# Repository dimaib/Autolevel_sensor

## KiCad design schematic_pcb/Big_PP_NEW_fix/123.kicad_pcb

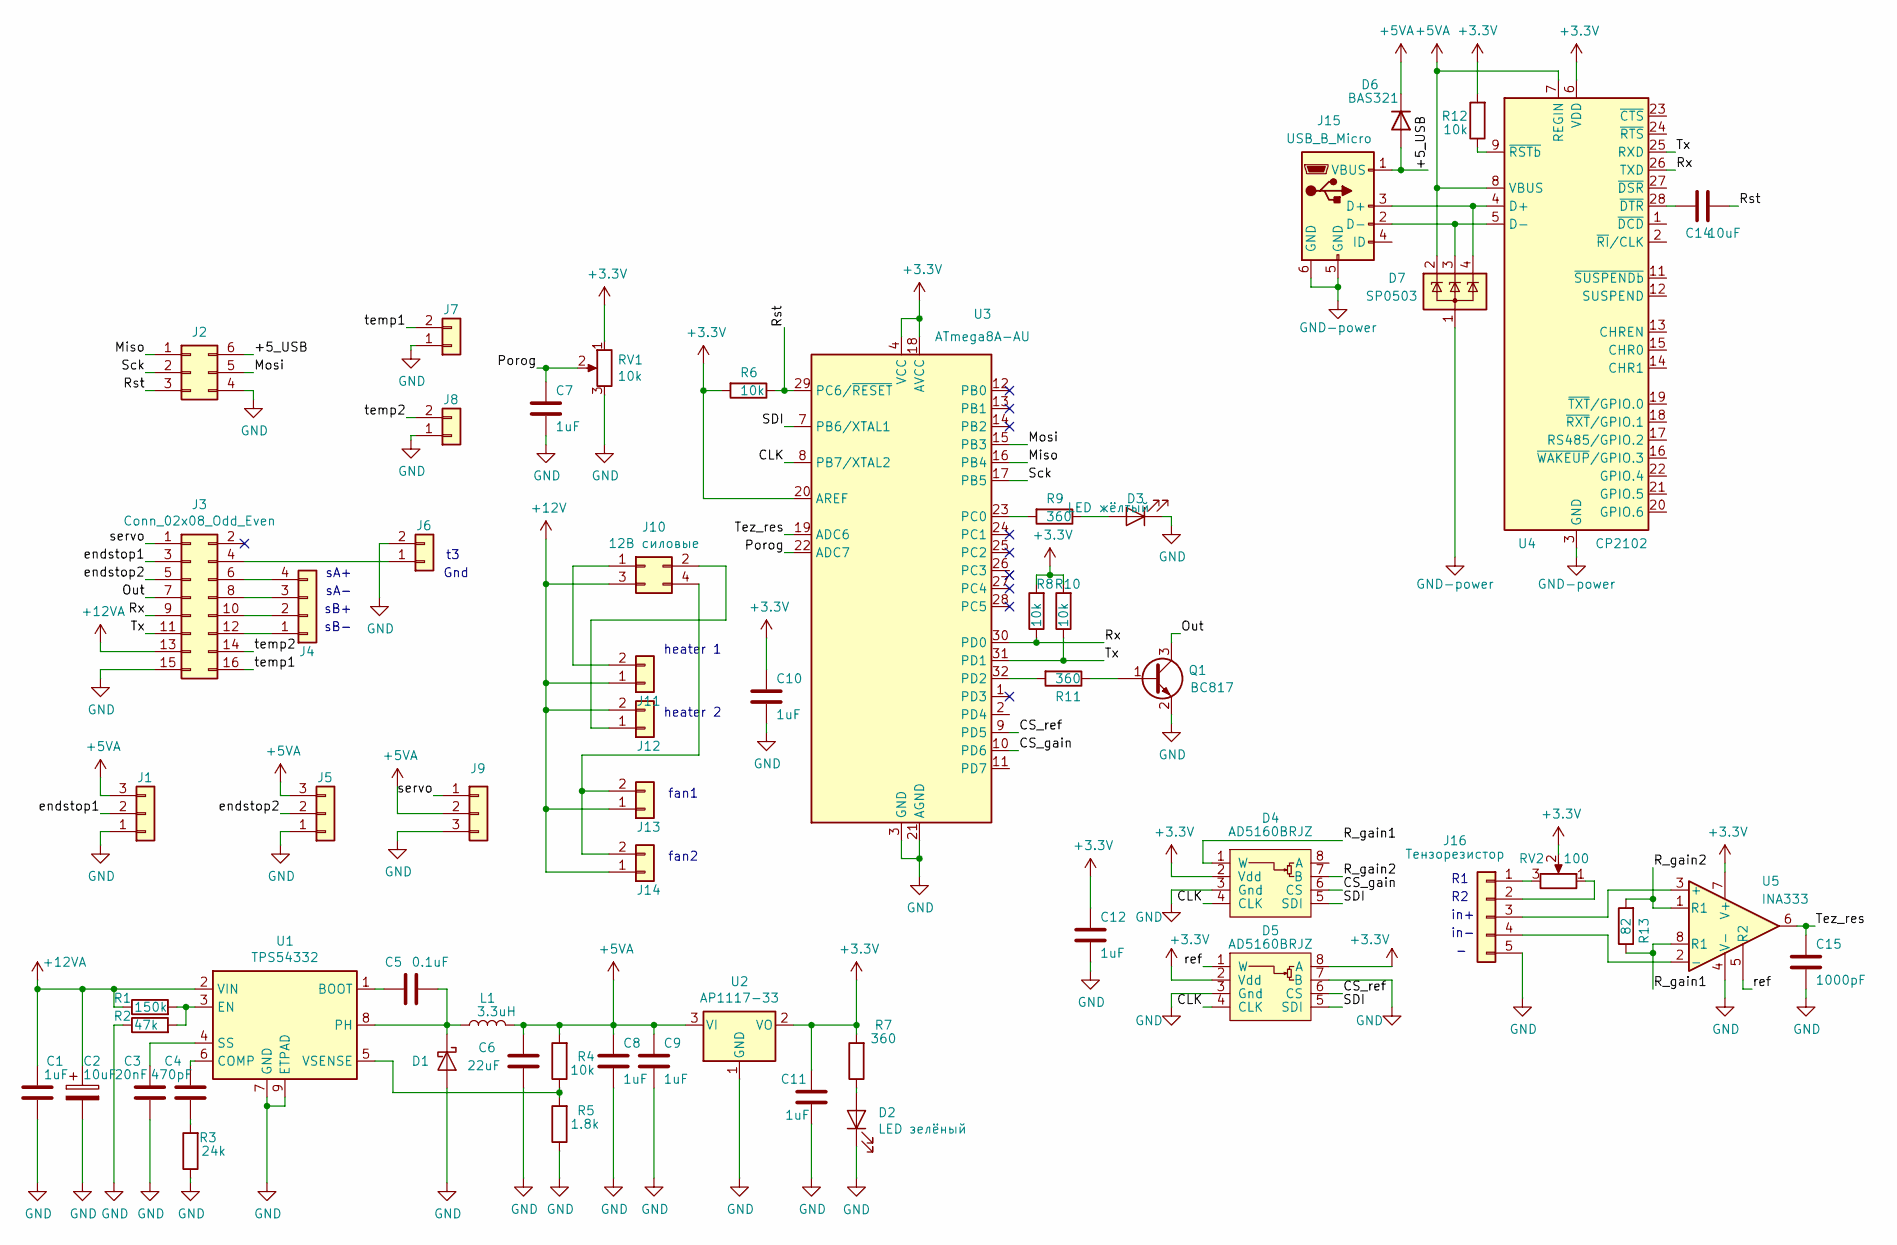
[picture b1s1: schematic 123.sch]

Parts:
C1, C7, C8, C9, C10, C11, C12: 1uF; C_0603_1608Metric
C2: 10uF; CP_EIA-3528-21_Kemet-B
C3: 20nF; C_0603_1608Metric
C4: 470pF; C_0603_1608Metric
C5: 0.1uF; C_0603_1608Metric
C6: 22uF; C_0805_2012Metric
C14: 10uF; C_0603_1608Metric
C15: 1000pF; C_0603_1608Metric
D1: Диод Шоттки; D_SMA
D2: LED зелёный; LED_D3.0mm_Horizontal_O6.35mm_Z2.0mm
D3: LED жёлтый; LED_D3.0mm_Horizontal_O6.35mm_Z2.0mm
D4, D5: AD5160BRJZ; SOT-23-8
D6: BAS321; D_SOD-323_HandSoldering
D7: SP0503; SOT-143
J1, J5: Conn_01x03; JST_XH_B3B-XH-A_1x03_P2.50mm_Vertical
J2: Conn_02x03_Counter_Clockwise; PinHeader_2x03_P2.54mm_Vertical
J3: Conn_02x08_Odd_Even; IDC-Header_2x08_P2.54mm_Vertical
J4: Conn_01x04; JST_XH_B4B-XH-A_1x04_P2.50mm_Vertical
J6, J7, J8, J13, J14: Conn_01x02; JST_XH_B2B-XH-A_1x02_P2.50mm_Vertical
J9: Conn_01x03; PinHeader_1x03_P2.54mm_Vertical
J10: 12В силовые; PhoenixContact_MCV_1,5_4-G-3.81_1x04_P3.81mm_Vertical
J11, J12: Conn_01x02; PhoenixContact_MCV_1,5_2-G-3.81_1x02_P3.81mm_Vertical
J15: USB_B_Micro; USB_Mini-B_Lumberg_2486_01_Horizontal
J16: Тензорезистор; PinHeader_1x05_P2.54mm_Vertical
L1: 3.3uH; L_Radial_D8.7mm_P5.00mm_Fastron_07HCP
Q1: BC817; SOT-23
R1: 150k; R_0603_1608Metric
R2: 47k; R_0603_1608Metric
R3: 24k; R_0603_1608Metric
R4, R6, R8, R10, R12: 10k; R_0603_1608Metric
R5: 1.8k; R_0603_1608Metric
R7, R9, R11: 360; R_0603_1608Metric
R13: 82; R_0603_1608Metric
RV1: 10k; Potentiometer_Bourns_3296W_Vertical
RV2: 100; 3224W
U1: TPS54332; TI_SO-PowerPAD-8_ThermalVias
U2: AP1117-33; SOT-223-3_TabPin2
U3: ATmega8A-AU; TQFP-32_7x7mm_P0.8mm
U4: CP2102; QFN-28-1EP_5x5mm_P0.5mm_EP3.35x3.35mm
U5: INA333; MSOP-8_3x3mm_P0.65mm

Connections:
+3V3: C10.1, C11.1, C12.1, D4.2 (Vdd), D5.2 (Vdd), D5.8 (A), R6.2, R7.2, R8.2, R10.2, R12.2, RV1.1, RV2.2, U2.2 (VO), U3.4 (VCC), U3.6 (VCC), U3.18 (AVCC), U3.20 (AREF), U4.6 (VDD), U5.7 (V+)
+5VA: C6.2, C8.1, C9.1, D6.2 (K), D7.2 (K), J1.3, J5.3, J9.2, L1.2, R4.2, U2.3 (VI), U4.7 (REGIN), U4.8 (VBUS)
+12V: J10.3, J11.1, J12.2, J13.1, J14.1
+12VA: C1.2, C2.1, J3.13, R1.1, U1.2 (VIN)
/+5_USB: D6.1 (A), J2.6, J15.1 (VBUS)
/CLK: D4.4 (CLK), D5.4 (CLK), U3.8 (PB7/XTAL2)
/CS_gain: D4.6 (CS), U3.10 (PD6)
/CS_ref: D5.6 (CS), U3.9 (PD5)
/Miso: J2.1, U3.16 (PB4)
/Mosi: J2.5, U3.15 (PB3)
/Out: J3.7, Q1.3 (C)
/Porog: C7.1, RV1.2, U3.22 (ADC7)
/R_gain1: D4.1 (W), R13.1, U5.8 (R1)
/R_gain2: D4.7 (B), R13.2, U5.1 (R1)
/Rst: C14.1, J2.3, R6.1, U3.29 (PC6/~RESET)
/Rx: J3.9, R8.1, U3.30 (PD0), U4.26 (TXD)
/SDI: D4.5 (SDI), D5.5 (SDI), U3.7 (PB6/XTAL1)
/Sck: J2.2, U3.17 (PB5)
/Tez_res: C15.1, U3.19 (ADC6), U5.6
/Tx: J3.11, R10.1, U3.31 (PD1), U4.25 (RXD)
/endstop1: J1.2, J3.3
/endstop2: J3.5, J5.2
/ref: D5.1 (W), U5.5 (R2)
/servo: J3.1, J9.1
/temp1: J3.16, J7.2
/temp2: J3.14, J8.2
unnamed: C3.1, U1.4 (SS)
unnamed: C4.1, U1.6 (COMP)
unnamed: C4.2, R3.2
unnamed: C5.1, D1.1 (K), L1.1, U1.8 (PH)
unnamed: C5.2, U1.1 (BOOT)
unnamed: C14.2, U4.28 (~DTR)
unnamed: D2.2 (A), R7.1
unnamed: D3.2 (A), R9.1
unnamed: D7.3 (K), J15.2 (D-), U4.5 (D-)
unnamed: D7.4 (K), J15.3 (D+), U4.4 (D+)
unnamed: J3.4, J6.1
unnamed: J3.6, J4.4
unnamed: J3.8, J4.3
unnamed: J3.10, J4.2
unnamed: J3.12, J4.1
unnamed: J10.1, J11.2
unnamed: J10.2, J12.1
unnamed: J10.4, J13.2, J14.2
unnamed: J16.1, RV2.3
unnamed: J16.2, RV2.1
unnamed: J16.3, U5.3 (+)
unnamed: J16.4, U5.2 (-)
unnamed: Q1.1 (B), R11.1
unnamed: R1.2, R2.2, U1.3 (EN)
unnamed: R4.1, R5.2, U1.5 (VSENSE)
unnamed: R9.2, U3.23 (PC0)
unnamed: R11.2, U3.32 (PD2)
unnamed: R12.1, U4.9 (~RSTb)

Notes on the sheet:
fan1
fan2
heater 1
heater 2
sA+
sA-
sB+
sB-
Gnd
in+
in-

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
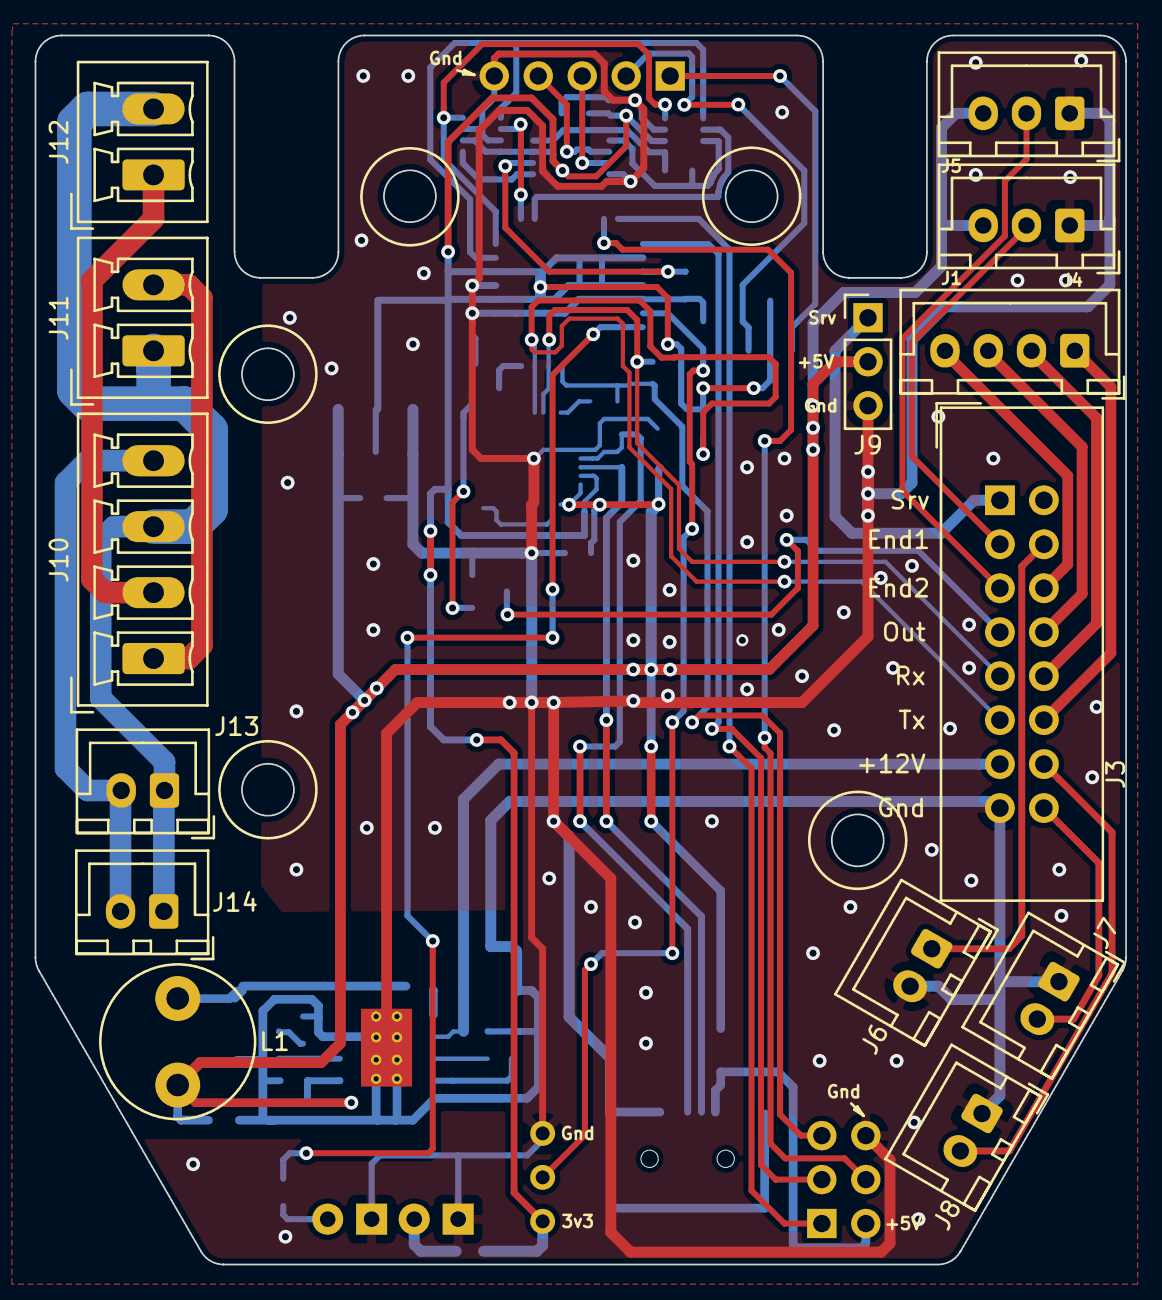
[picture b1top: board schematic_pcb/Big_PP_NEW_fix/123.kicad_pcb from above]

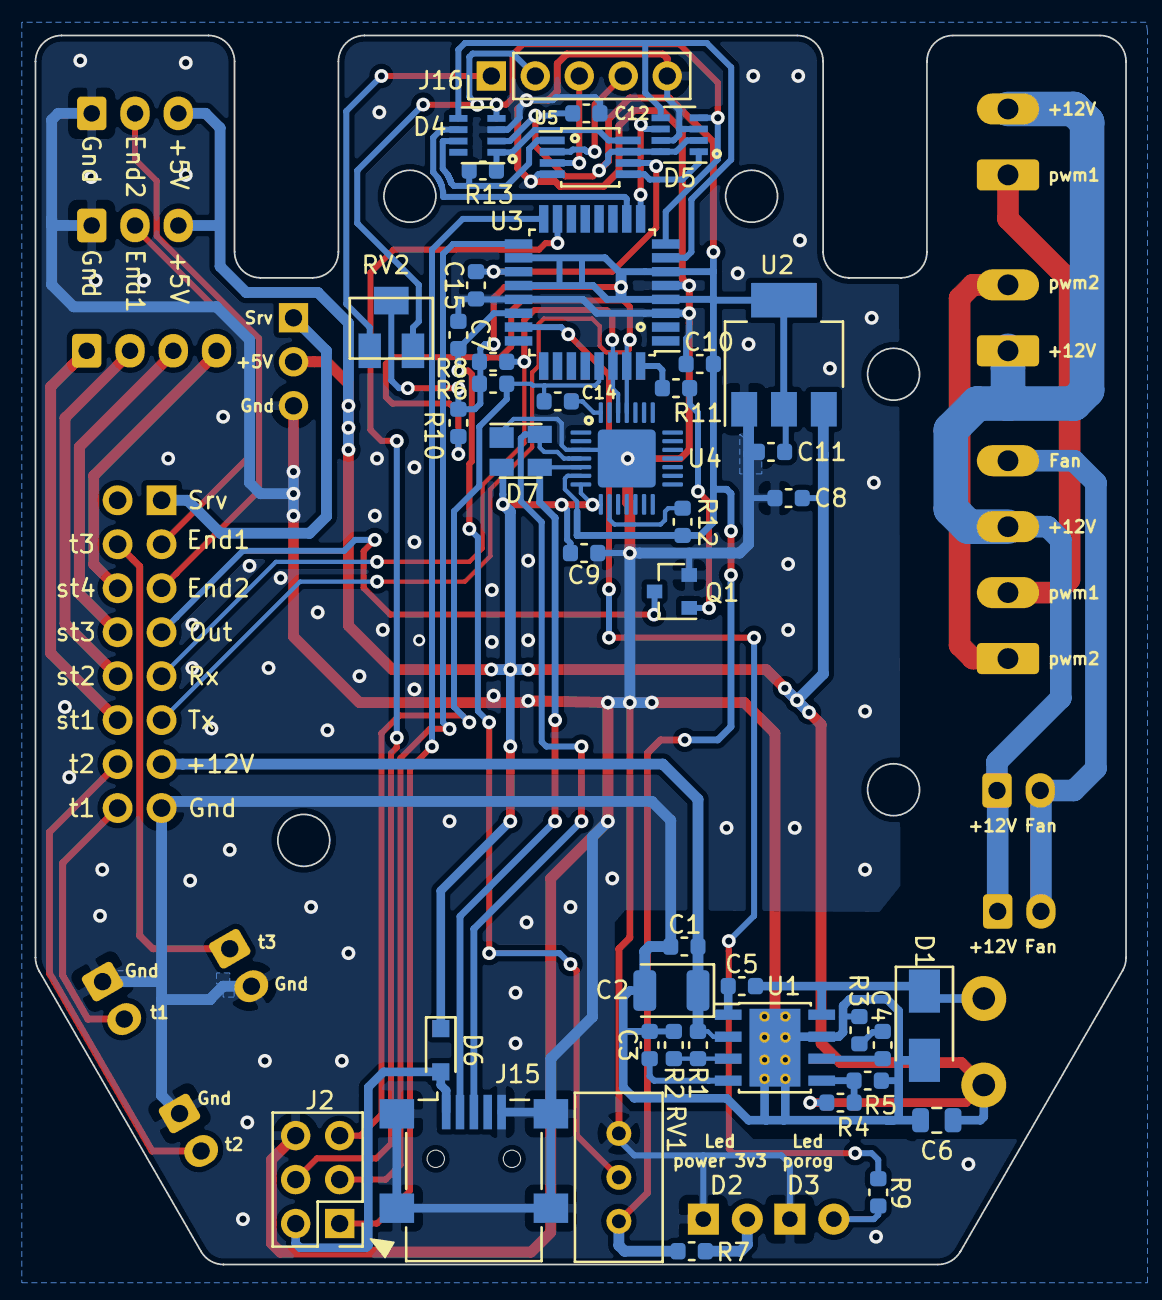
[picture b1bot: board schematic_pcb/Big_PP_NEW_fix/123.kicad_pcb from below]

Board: 2 copper layers, 63.0 x 71.0 mm, 59 parts (45 on the bottom side), 55 nets.

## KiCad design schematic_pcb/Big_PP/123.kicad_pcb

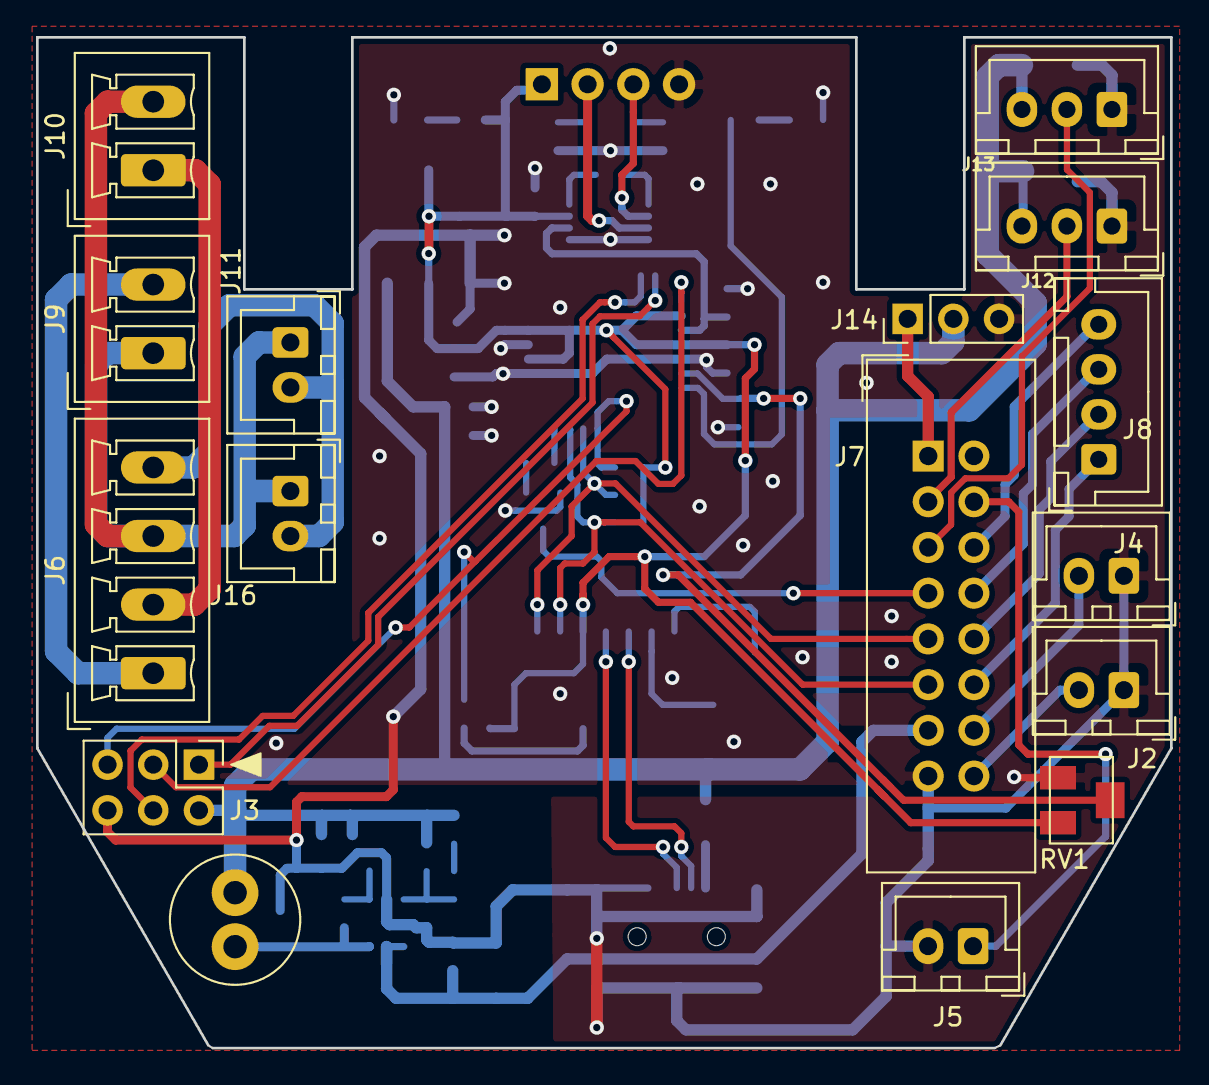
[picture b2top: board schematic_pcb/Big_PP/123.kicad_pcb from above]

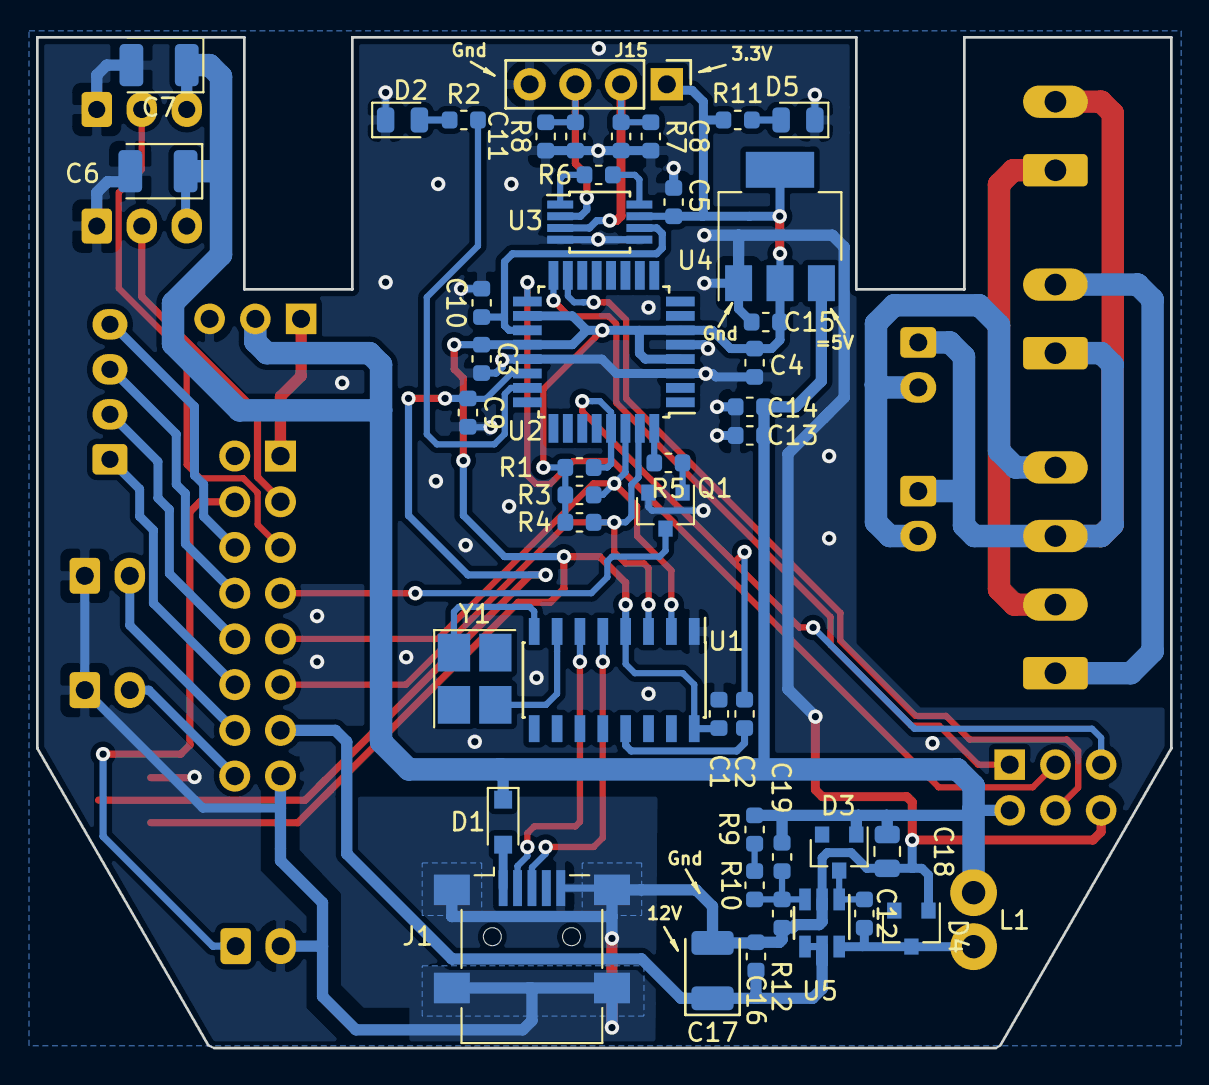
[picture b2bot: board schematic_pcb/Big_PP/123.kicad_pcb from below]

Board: 2 copper layers, 63.0 x 56.2 mm, 61 parts (45 on the bottom side), 46 nets.

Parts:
C1, C3, C4, C5, C8, C9, C10, C11, C13, C14, C15, C16: 1uF; C_0603_1608Metric
C2: 10uF; C_0603_1608Metric
C6, C7, C17: 10uF; CP_EIA-3528-21_Kemet-B
C12: 0.01uF; C_0603_1608Metric
C18: 22uF; C_0805_2012Metric
C19: 1000pF; C_0603_1608Metric
D1: BAS321; D_SOD-323_HandSoldering
D2, D5: LED; LED_0805_2012Metric
D3, D4: Диод Шоттки; D_SOT-23_ANK
J1: USB_B_Micro; USB_Mini-B_Lumberg_2486_01_Horizontal
J2, J4, J5, J11, J16: Conn_01x02; JST_XH_B2B-XH-A_1x02_P2.50mm_Vertical
J3: Conn_02x03_Counter_Clockwise; PinHeader_2x03_P2.54mm_Vertical
J6: 12В силовые; PhoenixContact_MCV_1,5_4-G-3.81_1x04_P3.81mm_Vertical
J7: Conn_02x08_Odd_Even; IDC-Header_2x08_P2.54mm_Vertical
J8: Conn_01x04; JST_XH_B4B-XH-A_1x04_P2.50mm_Vertical
J9, J10: Conn_01x02; PhoenixContact_MCV_1,5_2-G-3.81_1x02_P3.81mm_Vertical
J12, J13: Conn_01x03; JST_XH_B3B-XH-A_1x03_P2.50mm_Vertical
J14: Conn_01x03; PinHeader_1x03_P2.54mm_Vertical
J15: Тензорезистор; PinHeader_1x04_P2.54mm_Vertical
L1: 10uH; L_Radial_D7.0mm_P3.00mm
Q1: BC817; SOT-23
R1, R3, R4, R12: 10k; R_0603_1608Metric
R2, R5, R11: 360; R_0603_1608Metric
R6: 83; R_0603_1608Metric
R7, R8: 200; R_0603_1608Metric
R9: 1.5k; R_0603_1608Metric
R10: 51k; R_0603_1608Metric
RV1: R_POT 2k; 3224W
U1: CH340G; SOIC-16_3.9x9.9mm_P1.27mm
U2: ATmega8A-AU; TQFP-32_7x7mm_P0.8mm
U3: INA333; MSOP-8_3x3mm_P0.65mm
U4: AP1117-33; SOT-223-3_TabPin2
U5: LM2734Y; TSOT-23-6
Y1: 12MHz; Crystal_SMD_3225-4Pin_3.2x2.5mm_HandSoldering

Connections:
+3V3: C1.1, C3.1, C4.1, C5.1, C15.1, J15.1, R1.2, R3.2, R4.2, R11.2, RV1.1, U1.4, U1.16, U2.4, U2.6, U2.18, U2.20, U3.7, U4.2
+5VA: C6.1, C7.1, C13.1, C14.1, C18.2, C19.2, D1.2, D3.2, J3.6, J12.3, J13.3, J14.2, L1.2, R9.1, U4.3
+12V: J6.3, J9.1, J10.2, J11.1, J16.1
+12VA: C16.2, C17.1, J7.13, U5.4, U5.5
/Fb: C19.1, R10.1, R12.2, U5.3
/Miso: J3.1, U2.16
/Mosi: J3.5, U2.15
/Out: J7.7, Q1.3
/Porog: C9.1, RV1.2, U2.22
/Rst: C2.1, J3.3, R1.1, U2.29
/Rx: J7.9, R3.1, U1.2, U2.30
/Sck: J3.2, U2.17
/Tez_res: C10.1, U2.19, U3.6
/Tx: J7.11, R4.1, U1.3, U2.31
/endstop1: J7.3, J12.2
/endstop2: J7.5, J13.2
/servo: J7.1, J14.1
/temp1: J2.2, J7.16
/temp2: J4.2, J7.14
GND: C1.2, C3.2, C4.2, C5.2, C6.2, C7.2, C8.2, C9.2, C10.2, C11.1, C13.2, C14.2, C15.2, C16.1, C17.2, C18.1, D2.1, D4.2, D5.1, J1.5, J1.6, J2.1, J3.4, J4.1, J5.2, J7.15, J12.1, J13.1, J14.3, J15.4, Q1.2, R7.1, R8.1, R12.1, RV1.3, U1.1, U2.3, U2.5, U2.21, U3.4, U3.5, U4.1, U5.2
unnamed: C2.2, U1.13
unnamed: C8.1, J15.2, R7.2, U3.3
unnamed: C11.2, J15.3, R8.2, U3.2
unnamed: C12.1, D4.1, L1.1, U5.6
unnamed: C12.2, D3.1, U5.1
unnamed: D1.1, J1.1
unnamed: D2.2, R2.1
unnamed: D5.2, R11.1
unnamed: J1.2, U1.6
unnamed: J1.3, U1.5
unnamed: J5.1, J7.4
unnamed: J6.1, J9.2
unnamed: J7.6, J8.4
unnamed: J7.8, J8.3
unnamed: J7.10, J8.2
unnamed: J7.12, J8.1
unnamed: J6.2, J10.1
unnamed: J6.4, J11.2, J16.2
unnamed: Q1.1, R5.1
unnamed: R2.2, U2.23
unnamed: R5.2, U2.32
unnamed: R6.1, U3.8
unnamed: R6.2, U3.1
unnamed: R9.2, R10.2
unnamed: U1.7, Y1.2
unnamed: U1.8, Y1.1
